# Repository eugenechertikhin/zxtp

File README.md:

# ZX Tape Player

another implementatation tape player for casette player for retro computers

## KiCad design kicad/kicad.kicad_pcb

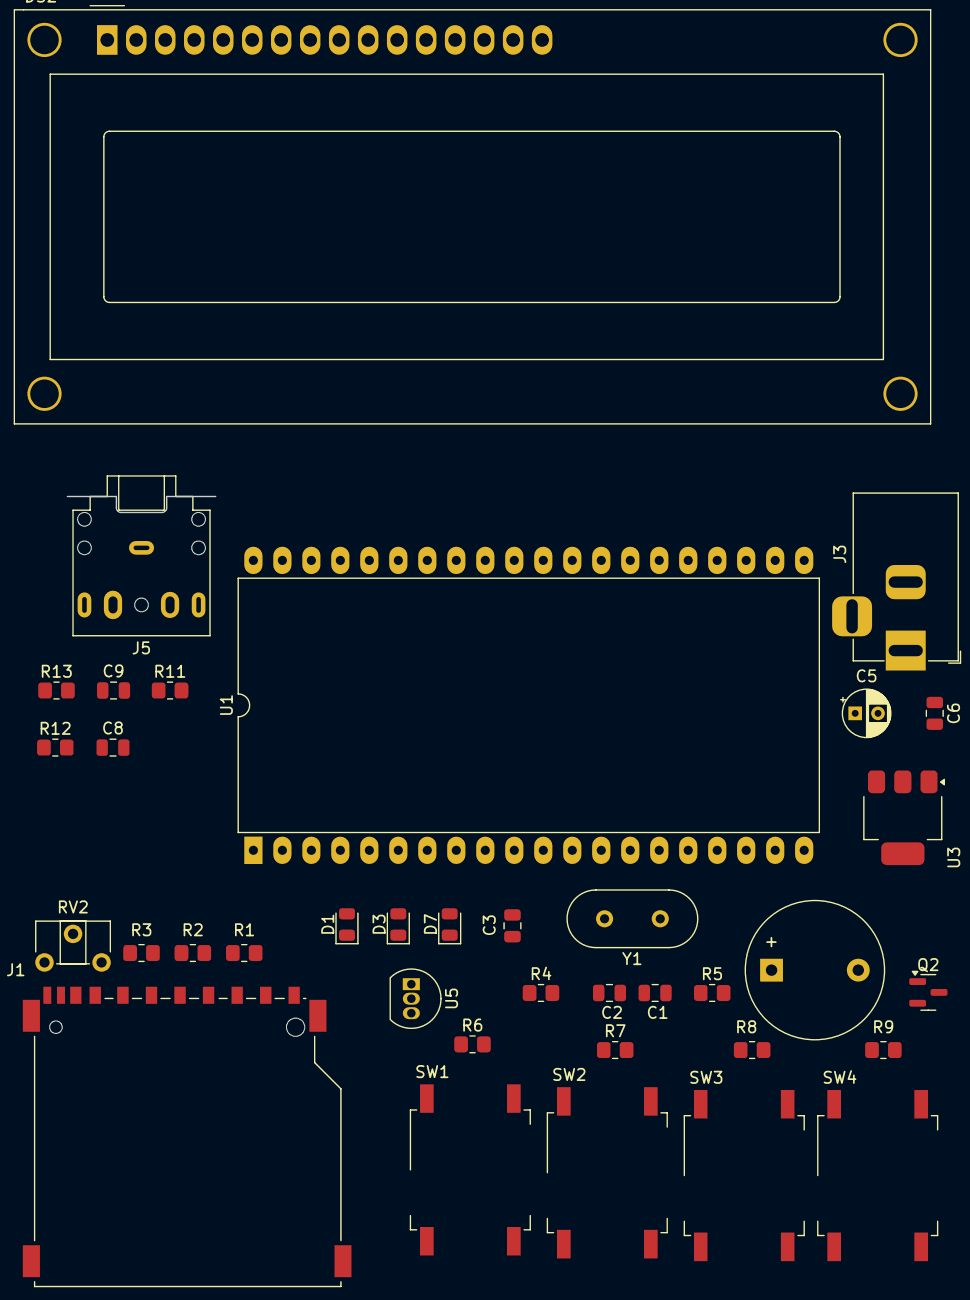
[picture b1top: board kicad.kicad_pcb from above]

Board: 2 copper layers, 37 parts (0 on the bottom side), 30 nets, no tracks yet.

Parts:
C1, C2: 18pF; C_0805_2012Metric
C3: 10nF; C_0805_2012Metric
C5: 10uF; CP_Radial_D4.0mm_P2.00mm
C6, C8, C9: 0.1uF; C_0805_2012Metric
D1, D3, D7: 1N4004; D_0805_2012Metric
DS2: WC1602A
J1: Micro_SD_Card; SD_TE_2041021
J2: Speaker; Buzzer_12x9.5RM7.6
J3: BarrelJack_Horizontal
J5: AudioJack; Jack_3.5mm_CUI_SJ1-3525N_Horizontal
Q2: BC847; SOT-23
R1, R2, R3, R6, R7, R8, R9, R11, R12, R13: 1k; R_0805_2012Metric_Pad1.20x1.40mm_HandSolder
R4: 10k; R_0805_2012Metric_Pad1.20x1.40mm_HandSolder
R5: 300r; R_0805_2012Metric_Pad1.20x1.40mm_HandSolder
RV2: 5k; Potentiometer_ACP_CA6-H2,5_Horizontal
SW1, SW2, SW3, SW4: SW_MEC_5E; SW_MEC_5GSH9
U1: ATmega16A-P; DIP-40_W25.4mm_LongPads
U3: AMS1117; SOT-223-3_TabPin2
U5: LP2950; TO-92_Inline
Y1: 16Mhz; Crystal_HC49-4H_Vertical

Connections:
+5V: DS2.2 (VDD), DS2.15 (LED(+)), Q2.3 (C), R4.2, RV2.3, SW1.1, SW1.2, SW2.1, SW2.2, SW3.1, SW3.2, SW4.1, SW4.2, U1.10 (VCC), U1.30 (AVCC), U3.2 (VO), U5.3 (VI)
DISP_D4: DS2.11 (D4), U1.24 (PC2)
DISP_D5: DS2.12 (D5), U1.25 (PC3)
DISP_D6: DS2.13 (D6), U1.26 (PC4)
DISP_D7: DS2.14 (D7), U1.27 (PC5)
DISP_E: DS2.6 (E), U1.28 (PC6)
DISP_RS: DS2.4 (RS), U1.29 (PC7)
GND: C1.1, C2.1, C3.1, C5.2, C6.2, C8.2, DS2.1 (VSS), DS2.5 (R/W), J1.6 (VSS), J1.9 (SHIELD), J3.2, R1.2, R2.2, R3.2, R5.2, R6.2, R7.2, R8.2, R9.2, R12.2, U1.11 (GND), U1.31 (GND), U3.1 (GND), U5.2 (GND)
unnamed: C8.1, C9.2, R11.2, R12.1
unnamed: C9.1, J5.S, R13.1
unnamed: D1.2 (A), U1.5 (PB4)
unnamed: D1.1 (K), J1.2 (DAT3/CD), R1.1
unnamed: D3.2 (A), U1.6 (PB5)
unnamed: D3.1 (K), J1.3 (CMD), R2.1
unnamed: D7.2 (A), U1.8 (PB7)
unnamed: D7.1 (K), J1.5 (CLK), R3.1
unnamed: DS2.16 (LED(-)), RV2.1
unnamed: DS2.3 (VO), RV2.2
unnamed: J1.7 (DAT0), U1.7 (PB6)
unnamed: J5.T, J5.TN, R13.2
unnamed: C1.2, U1.13 (XTAL1), Y1.1
unnamed: C2.2, U1.12 (XTAL2), Y1.2
unnamed: C3.2, R4.1, U1.9 (~RESET)
unnamed: C5.1, C6.1, J3.1, U3.3 (VI)
S1: R6.1, SW1.3 (K), SW1.4 (A), U1.15 (PD1)
S2: R7.1, SW2.3 (K), SW2.4 (A), U1.16 (PD2)
S3: R8.1, SW3.3 (K), SW3.4 (A), U1.17 (PD3)
S4: R9.1, SW4.3 (K), SW4.4 (A), U1.18 (PD4)
SND_OUT: Q2.1 (B), R11.1, U1.14 (PD0)
VCC33: J1.4 (VDD), U5.1 (VO)

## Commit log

2025-07-07 initial
